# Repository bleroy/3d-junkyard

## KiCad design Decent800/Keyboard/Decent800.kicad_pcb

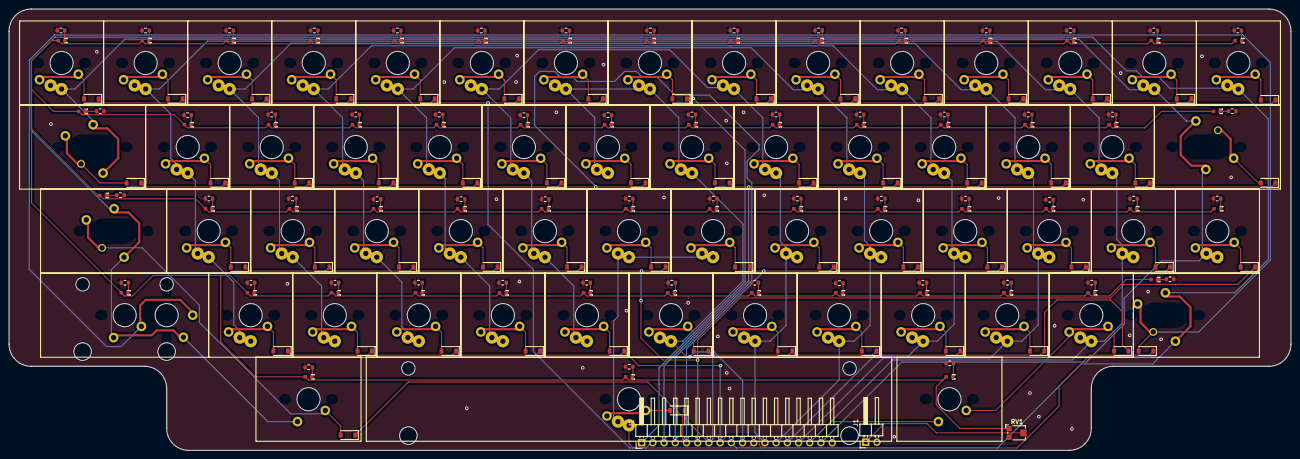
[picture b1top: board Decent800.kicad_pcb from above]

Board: 2 copper layers, 290.5 x 100.0 mm, 177 parts (0 on the bottom side), 135 nets.

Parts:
D1, D2, D3, D5, D6, D7, D8, D10, D12, D13, D14, D15, D16, D17, D18, D19, D20, D21, D22, D24, D25, D26, D27, D28, D29, D30, D31, D32, D33, D34, D35, D36, D37, D38, D39, D41, D42, D43, D44, D45, D46, D47, D48, D49, D50, D51, D52, D53, D54, D55, D56, D57, D58, D59, D60, D62: 1N4148W; D_SOD-123
J1: Conn_01x02_Pin; PinHeader_1x02_P2.54mm_Horizontal
J2: Conn_01x18; PinHeader_1x18_P2.54mm_Horizontal
R1, R2, R3, R4, R5, R7, R8, R9, R10, R11, R12, R14, R15, R16, R17, R18, R19, R20, R21, R22, R23, R24, R25, R26, R27, R28, R29, R30, R31, R32, R33, R34, R35, R36, R37, R38, R39, R40, R42, R43, R44, R45, R46, R47, R48, R49, R50, R51, R52, R53, R54, R55, R56, R57, R59, R60, R61, R62, R64: 100; R_0603_1608Metric
RV1: R_Potentiometer; Potentiometer_Bourns_TC33X_Vertical
SW0: 0; MX-1-00U-LED
SW1: 1; MX-1-00U-LED
SW2: 2; MX-1-00U-LED
SW3: 3; MX-1-00U-LED
SW4: 4; MX-1-00U-LED
SW5: 5; MX-1-00U-LED
SW6: 6; MX-1-00U-LED
SW7: 7; MX-1-00U-LED
SW8: 8; MX-1-00U-LED
SW9: 9; MX-1-00U-LED
SWA1: A; MX-1-00U-LED
SWAtari1: Atari; MX-1-00U-LED
SWAtari2: Atari; MX-1-25U-LED
SWB1: B; MX-1-00U-LED
SWBrk1: Break; MX-1-00U-LED
SWC1: C; MX-1-00U-LED
SWComma1: Comma; MX-1-00U-LED
SWCps1: Caps; MX-1-00U-LED
SWCtl1: Control; MX-1-50U-LED
SWCtl2: Control; MX-1-25U-LED
SWD1: D; MX-1-00U-LED
SWDash1: Dash; MX-1-00U-LED
SWDel1: Del; MX-1-00U-LED
SWE1: E; MX-1-00U-LED
SWEqual1: Equal; MX-1-00U-LED
SWEsc1: Esc; MX-1-00U-LED
SWF1: F; MX-1-00U-LED
SWG1: G; MX-1-00U-LED
SWGT1: GreaterThan; MX-1-00U-LED
SWH1: H; MX-1-00U-LED
SWI1: I; MX-1-00U-LED
SWJ1: J; MX-1-00U-LED
SWK1: K; MX-1-00U-LED
SWL1: L; MX-1-00U-LED
SWLT1: LessThan; MX-1-00U-LED
SWLeftSft1: Shift; MX-2-00U-LED
SWM1: M; MX-1-00U-LED
SWN1: N; MX-1-00U-LED
SWO1: O; MX-1-00U-LED
SWP1: P; MX-1-00U-LED
SWPeriod1: Period; MX-1-00U-LED
SWPlus1: Plus; MX-1-00U-LED
SWQ1: Q; MX-1-00U-LED
SWR1: R; MX-1-00U-LED
SWRet1: Return; MX-1-50U-LED-Right
SWRightSft1: Shift; MX-2-50U-LED
SWS1: S; MX-1-00U-LED
SWSemi1: Semicolon; MX-1-00U-LED
SWSlash1: Slash; MX-1-00U-LED
SWSpc1: Space; MX-6-25U-LED
SWStar1: Star; MX-1-00U-LED
SWT1: T; MX-1-00U-LED
SWTab1: Tab; MX-1-50U-LED
SWU1: U; MX-1-00U-LED
SWV1: V; MX-1-00U-LED
SWW1: W; MX-1-00U-LED
SWX1: X; MX-1-00U-LED
SWY1: Y; MX-1-00U-LED
SWZ1: Z; MX-1-00U-LED

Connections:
5V: J1.1, RV1.2
COL_1: J2.10, SW6.1, SW7.1, SWN1.1, SWU1.1, SWY1.1
COL_2: J2.11, SWH1.1, SWJ1.1, SWSpc1.1
COL_3: J2.12, SW5.1, SW8.1, SWB1.1, SWG1.1, SWI1.1, SWK1.1, SWM1.1, SWT1.1
COL_4: J2.13, SW4.1, SW9.1, SWComma1.1, SWF1.1, SWL1.1, SWO1.1, SWR1.1, SWV1.1
COL_5: J2.14, SW0.1, SW3.1, SWC1.1, SWD1.1, SWE1.1, SWP1.1, SWPeriod1.1, SWSemi1.1
COL_6: J2.15, SW2.1, SWDash1.1, SWLT1.1, SWPlus1.1, SWS1.1, SWSlash1.1, SWW1.1, SWX1.1
COL_7: J2.16, SW1.1, SWA1.1, SWAtari1.1, SWAtari2.1, SWEqual1.1, SWGT1.1, SWQ1.1, SWStar1.1, SWZ1.1
COL_8: J2.17, SWCps1.1, SWDel1.1, SWEsc1.1, SWRet1.1, SWTab1.1
COL_9: J2.9, SWBrk1.1, SWCtl1.1, SWCtl2.1, SWLeftSft1.1, SWRightSft1.1
LED_GND: J1.2, R1.2, R2.2, R3.2, R4.2, R5.2, R7.2, R8.2, R9.2, R10.2, R11.2, R12.2, R14.2, R15.2, R16.2, R17.2, R18.2, R19.2, R20.2, R21.2, R22.2, R23.2, R24.2, R25.2, R26.2, R27.2, R28.2, R29.2, R30.2, R31.2, R32.2, R33.2, R34.2, R35.2, R36.2, R37.2, R38.2, R39.2, R40.2, R42.2, R43.2, R44.2, R45.2, R46.2, R47.2, R48.2, R49.2, R50.2, R51.2, R52.2, R53.2, R54.2, R55.2, R56.2, R57.2, R59.2, R60.2, R61.2, R62.2, R64.2
unnamed: D1.2 (A), SWBrk1.2
unnamed: D2.2 (A), SWCtl1.2, SWCtl2.2
unnamed: D3.2 (A), SWLeftSft1.2, SWRightSft1.2
unnamed: D5.2 (A), SW7.2
unnamed: D6.2 (A), SW6.2
unnamed: D7.2 (A), SWU1.2
unnamed: D8.2 (A), SWY1.2
unnamed: D10.2 (A), SWN1.2
unnamed: D12.2 (A), SWJ1.2
unnamed: D13.2 (A), SWH1.2
unnamed: D14.2 (A), SWSpc1.2
unnamed: D15.2 (A), SW8.2
unnamed: D16.2 (A), SW5.2
unnamed: D17.2 (A), SWI1.2
unnamed: D18.2 (A), SWT1.2
unnamed: D19.2 (A), SWK1.2
unnamed: D20.2 (A), SWG1.2
unnamed: D21.2 (A), SWM1.2
unnamed: D22.2 (A), SWB1.2
unnamed: D24.2 (A), SW9.2
unnamed: D25.2 (A), SW4.2
unnamed: D26.2 (A), SWO1.2
unnamed: D27.2 (A), SWR1.2
unnamed: D28.2 (A), SWL1.2
unnamed: D29.2 (A), SWF1.2
unnamed: D30.2 (A), SWComma1.2
unnamed: D31.2 (A), SWV1.2
unnamed: D32.2 (A), SW0.2
unnamed: D33.2 (A), SW3.2
unnamed: D34.2 (A), SWP1.2
unnamed: D35.2 (A), SWE1.2
unnamed: D36.2 (A), SWSemi1.2
unnamed: D37.2 (A), SWD1.2
unnamed: D38.2 (A), SWPeriod1.2
unnamed: D39.2 (A), SWC1.2
unnamed: D41.2 (A), SWLT1.2
unnamed: D42.2 (A), SW2.2
unnamed: D43.2 (A), SWDash1.2
unnamed: D44.2 (A), SWW1.2
unnamed: D45.2 (A), SWPlus1.2
unnamed: D46.2 (A), SWS1.2
unnamed: D47.2 (A), SWSlash1.2
unnamed: D48.2 (A), SWX1.2
unnamed: D49.2 (A), SWGT1.2
unnamed: D50.2 (A), SW1.2
unnamed: D51.2 (A), SWEqual1.2
unnamed: D52.2 (A), SWQ1.2
unnamed: D53.2 (A), SWStar1.2
unnamed: D54.2 (A), SWA1.2
unnamed: D55.2 (A), SWAtari1.2, SWAtari2.2
unnamed: D56.2 (A), SWZ1.2
unnamed: D57.2 (A), SWDel1.2
unnamed: D58.2 (A), SWEsc1.2
unnamed: D59.2 (A), SWRet1.2
unnamed: D60.2 (A), SWTab1.2
unnamed: D62.2 (A), SWCps1.2
unnamed: R1.1, SWBrk1.3
unnamed: R2.1, SWAtari2.3
unnamed: R3.1, SWCtl1.3
unnamed: R4.1, SWLeftSft1.3
unnamed: R5.1, SWRightSft1.3
unnamed: R7.1, SW7.3
unnamed: R8.1, SW6.3
unnamed: R9.1, SWU1.3
unnamed: R10.1, SWY1.3
unnamed: R11.1, SWCtl2.3
unnamed: R12.1, SWN1.3
unnamed: R14.1, SWJ1.3
unnamed: R15.1, SWH1.3
unnamed: R16.1, SWSpc1.3
unnamed: R17.1, SW8.3
unnamed: R18.1, SW5.3
unnamed: R19.1, SWI1.3
unnamed: R20.1, SWT1.3
unnamed: R21.1, SWK1.3
unnamed: R22.1, SWG1.3
unnamed: R23.1, SWM1.3
unnamed: R24.1, SWB1.3
unnamed: R25.1, SW9.3
unnamed: R26.1, SW4.3
unnamed: R27.1, SWO1.3
unnamed: R28.1, SWR1.3
unnamed: R29.1, SWL1.3
unnamed: R30.1, SWF1.3
unnamed: R31.1, SWComma1.3
unnamed: R32.1, SWV1.3
unnamed: R33.1, SW0.3
unnamed: R34.1, SW3.3
unnamed: R35.1, SWP1.3
unnamed: R36.1, SWE1.3
unnamed: R37.1, SWSemi1.3
unnamed: R38.1, SWD1.3
unnamed: R39.1, SWPeriod1.3
unnamed: R40.1, SWC1.3
unnamed: R42.1, SWLT1.3
unnamed: R43.1, SW2.3
unnamed: R44.1, SWDash1.3
unnamed: R45.1, SWW1.3
unnamed: R46.1, SWPlus1.3
unnamed: R47.1, SWS1.3
unnamed: R48.1, SWSlash1.3
unnamed: R49.1, SWX1.3
unnamed: R50.1, SWGT1.3
unnamed: R51.1, SW1.3
unnamed: R52.1, SWEqual1.3
unnamed: R53.1, SWQ1.3
unnamed: R54.1, SWStar1.3
unnamed: R55.1, SWA1.3
unnamed: R56.1, SWAtari1.3
unnamed: R57.1, SWZ1.3
unnamed: R59.1, SWDel1.3
unnamed: R60.1, SWEsc1.3
unnamed: R61.1, SWRet1.3
unnamed: R62.1, SWTab1.3
unnamed: R64.1, SWCps1.3
ROW_1: D1.1 (K), D5.1 (K), D15.1 (K), D24.1 (K), D32.1 (K), D41.1 (K), D49.1 (K), D57.1 (K), J2.1
ROW_2: D6.1 (K), D16.1 (K), D25.1 (K), D33.1 (K), D42.1 (K), D50.1 (K), D58.1 (K), J2.2
ROW_3: D7.1 (K), D17.1 (K), D26.1 (K), D34.1 (K), D43.1 (K), D51.1 (K), D59.1 (K), J2.3
ROW_4: D8.1 (K), D18.1 (K), D27.1 (K), D35.1 (K), D44.1 (K), D52.1 (K), D60.1 (K), J2.4
ROW_5: D2.1 (K), D12.1 (K), D19.1 (K), D28.1 (K), D36.1 (K), D45.1 (K), D53.1 (K), J2.5
ROW_6: D13.1 (K), D20.1 (K), D29.1 (K), D37.1 (K), D46.1 (K), D54.1 (K), D62.1 (K), J2.6
ROW_7: D10.1 (K), D14.1 (K), D21.1 (K), D30.1 (K), D38.1 (K), D47.1 (K), D55.1 (K), J2.7
ROW_8: D3.1 (K), D22.1 (K), D31.1 (K), D39.1 (K), D48.1 (K), D56.1 (K), J2.8
VCC_LED: RV1.1, SW0.4, SW1.4, SW2.4, SW3.4, SW4.4, SW5.4, SW6.4, SW7.4, SW8.4, SW9.4, SWA1.4, SWAtari1.4, SWAtari2.4, SWB1.4, SWBrk1.4, SWC1.4, SWComma1.4, SWCps1.4, SWCtl1.4, SWCtl2.4, SWD1.4, SWDash1.4, SWDel1.4, SWE1.4, SWEqual1.4, SWEsc1.4, SWF1.4, SWG1.4, SWGT1.4, SWH1.4, SWI1.4, SWJ1.4, SWK1.4, SWL1.4, SWLT1.4, SWLeftSft1.4, SWM1.4, SWN1.4, SWO1.4, SWP1.4, SWPeriod1.4, SWPlus1.4, SWQ1.4, SWR1.4, SWRet1.4, SWRightSft1.4, SWS1.4, SWSemi1.4, SWSlash1.4, SWSpc1.4, SWStar1.4, SWT1.4, SWTab1.4, SWU1.4, SWV1.4, SWW1.4, SWX1.4, SWY1.4, SWZ1.4

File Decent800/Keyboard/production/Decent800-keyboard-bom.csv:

Designator,Footprint,Quantity,Value,LCSC Part #
"D1, D10, D12, D13, D14, D15, D16, D17, D18, D19, D2, D20, D21, D22, D24, D25, D26, D27, D28, D29, D3, D30, D31, D32, D33, D34, D35, D36, D37, D38, D39, D41, D42, D43, D44, D45, D46, D47, D48, D49, D5, D50, D51, D52, D53, D54, D55, D56, D57, D58, D59, D6, D60, D62, D7, D8",D_SOD-123,56,1N4148W,C81598
"R10, R11, R12, R14, R15, R16, R17, R18, R19, R2, R20, R21, R22, R23, R24, R25, R26, R27, R28, R29, R3, R30, R31, R32, R33, R34, R35, R36, R37, R38, R39, R4, R40, R42, R43, R44, R45, R46, R47, R48, R49, R5, R50, R51, R52, R53, R54, R55, R56, R57, R6, R60, R61, R62, R64, R7, R8, R9",0603,58,100,C22775
RV1,Potentiometer_Bourns_TC33X_Vertical,1,R_Potentiometer,C720647
SW0,MX-1-00U-LED,1,0,C193191
SW1,MX-1-00U-LED,1,1,C193191
SW2,MX-1-00U-LED,1,2,C193191
SW3,MX-1-00U-LED,1,3,C193191
SW4,MX-1-00U-LED,1,4,C193191
SW5,MX-1-00U-LED,1,5,C193191
SW6,MX-1-00U-LED,1,6,C193191
SW7,MX-1-00U-LED,1,7,C193191
SW8,MX-1-00U-LED,1,8,C193191
SW9,MX-1-00U-LED,1,9,C193191
SWA1,MX-1-00U-LED,1,A,C193191
SWAtari1,Choc-1-00U-LED,1,Atari,C193191
SWAtari2,MX-1-25U-LED,1,Atari,C193191
SWB1,MX-1-00U-LED,1,B,C193191
SWBrk2,MX-1-25U-LED,1,Break,C193191
SWC1,MX-1-00U-LED,1,C,C193191
SWComma1,MX-1-00U-LED,1,Comma,C193191
SWCps1,MX-1-00U-LED,1,Caps,C193191
SWCtl1,MX-1-50U-LED,1,Control,C193191
SWD1,MX-1-00U-LED,1,D,C193191
SWDash1,MX-1-00U-LED,1,Dash,C193191
SWDel2,MX-2-00U-LED-Del,1,Del,C193191
SWE1,MX-1-00U-LED,1,E,C193191
SWEqual1,MX-1-00U-LED,1,Equal,C193191
SWEsc1,MX-1-00U-LED,1,Esc,C193191
SWF1,MX-1-00U-LED,1,F,C193191
SWG1,MX-1-00U-LED,1,G,C193191
SWGT1,MX-1-00U-LED,1,GreaterThan,C193191
SWH1,MX-1-00U-LED,1,H,C193191
SWI1,MX-1-00U-LED,1,I,C193191
SWJ1,MX-1-00U-LED,1,J,C193191
SWK1,MX-1-00U-LED,1,K,C193191
SWL1,MX-1-00U-LED,1,L,C193191
SWLT1,MX-1-00U-LED,1,LessThan,C193191
SWLeftSft1,MX-2-00U-LED,1,Shift,C193191
SWM1,MX-1-00U-LED,1,M,C193191
SWN1,MX-1-00U-LED,1,N,C193191
SWO1,MX-1-00U-LED,1,O,C193191
SWP1,MX-1-00U-LED,1,P,C193191
SWPeriod1,MX-1-00U-LED,1,Period,C193191
SWPlus1,MX-1-00U-LED,1,Plus,C193191
SWQ1,MX-1-00U-LED,1,Q,C193191
SWR1,MX-1-00U-LED,1,R,C193191
SWRet1,MX-1-50U-LED-Right,1,Return,C193191
SWRightSft1,MX-2-25U-LED,1,Shift,C193191
SWS1,MX-1-00U-LED,1,S,C193191
SWSemi1,MX-1-00U-LED,1,Semicolon,C193191
SWSlash1,MX-1-00--1-25U-LED,1,Slash,C193191
SWSpc1,MX-6-25U-LED,1,Space,C193191
SWStar1,MX-1-00U-LED,1,Star,C193191
SWT1,MX-1-00U-LED,1,T,C193191
SWTab1,MX-1-50U-LED,1,Tab,C193191
SWU1,MX-1-00U-LED,1,U,C193191
SWV1,MX-1-00U-LED,1,V,C193191
SWW1,MX-1-00U-LED,1,W,C193191
SWX1,MX-1-00U-LED,1,X,C193191
SWY1,MX-1-00U-LED,1,Y,C193191
SWZ1,MX-1-00U-LED,1,Z,C193191

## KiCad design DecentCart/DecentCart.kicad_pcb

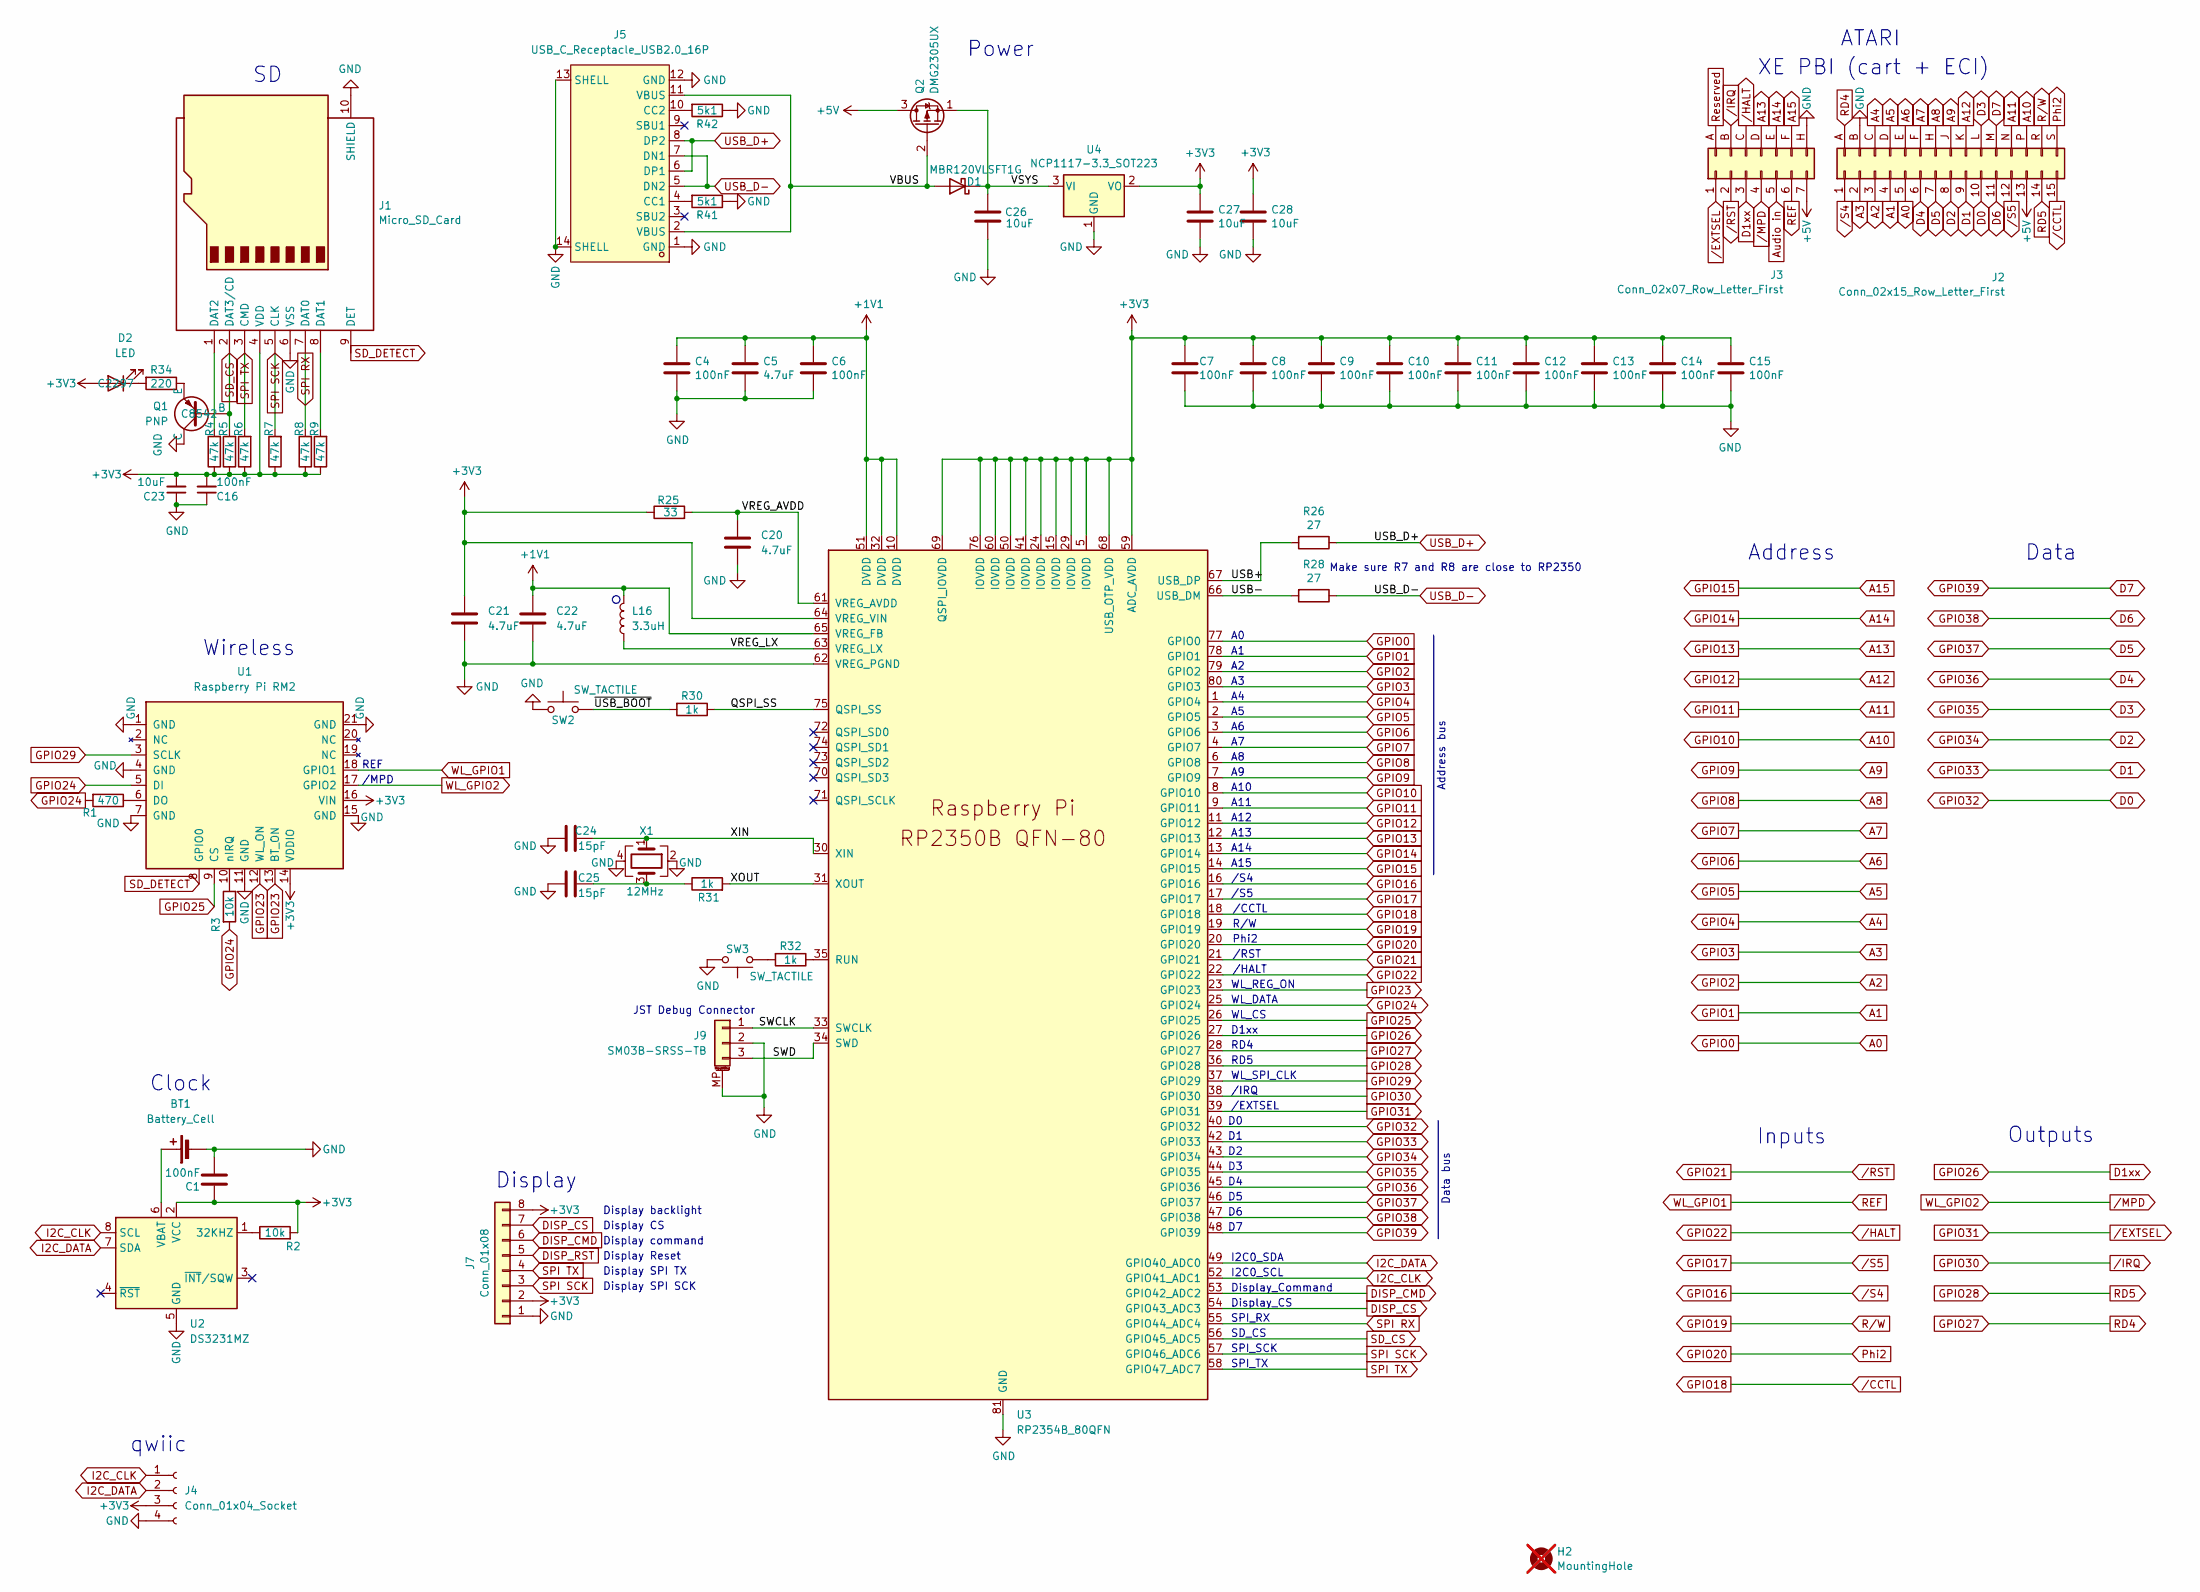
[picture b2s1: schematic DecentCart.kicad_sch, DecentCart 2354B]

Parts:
BT1: Battery_Cell; BAT-SMD_BS-CR2032-8; JLCPCB Part # C70377
C1, C4, C6, C7, C8, C9, C10, C11, C12, C13, C14, C15, C16: 100nF; C_0402_1005Metric; JLCPCB Part # C1525
C5, C20: 4.7uF; C_0402_1005Metric; JLCPCB Part # C23733
C21, C22: 4.7uF; C_0603_1608Metric; JLCPCB Part # C19666
C23, C26, C27, C28: 10uF; C_0402_1005Metric; JLCPCB Part # C15525
C24, C25: 15pF; C_0402_1005Metric; JLCPCB Part # C1548
D1: MBR120VLSFT1G; Nexperia_CFP3_SOD-123W; JLCPCB Part # C8598
D2: LED; D_0805_2012Metric; JLCPCB Part # C2297
H2: MountingHole; MountingHole_2.2mm_M2; not fitted
J1: Micro_SD_Card; TF-SMD_TF-PUSH; JLCPCB Part # C393941
J2: Conn_02x15_Row_Letter_First; Atari Cartridge Edge Connector
J3: Conn_02x07_Row_Letter_First; IDC-SMD_14P-P1.27_HXJN1.27-14P_ATARI_ECI; JLCPCB Part # C42455944
J4: Conn_01x04_Socket; CONN-SMD_4P-P1.00_SM04B-SRSS-TB-LF-SN; JLCPCB Part # C160404
J5: USB_C_Receptacle_USB2.0_16P; USB-C-SMD_TYPE-C-6PIN-2MD-073; JLCPCB Part # C2765186
J7: Conn_01x08; PinHeader_1x08_P2.54mm_Vertical
J9: SM03B-SRSS-TB; JST_SH_SM03B-SRSS-TB_1x03-1MP_P1.00mm_Horizontal; JLCPCB Part # C160389
L16: 3.3uH; IND-SMD_L2.0-W1.6_AOTA-B201610S3R3-101-T; JLCPCB Part # C42411119
Q1: PNP; SOT-23; JLCPCB Part # C8542
Q2: DMG2305UX; SOT-23; JLCPCB Part # C150470
R1: 470; R_0402_1005Metric; JLCPCB Part # C25117
R2, R3: 10k; R_0402_1005Metric; JLCPCB Part # C25744
R4, R5, R6, R7, R8, R9: 47k; R_0402_1005Metric; JLCPCB Part # C25792
R25: 33; R_0402_1005Metric; JLCPCB Part # C25105
R26, R28: 27; R_0805_2012Metric; JLCPCB Part # C17561
R30, R31, R32: 1k; R_0402_1005Metric; JLCPCB Part # C11702
R34: 220; R_0402_1005Metric; JLCPCB Part # C25091
R41, R42: 5k1; R_0402_1005Metric; JLCPCB Part # C25905
SW2, SW3: SW_TACTILE; Tactile_Switch_Basic_XKB_TS-1187A; JLCPCB Part # C318884
U1: Raspberry Pi RM2; rpi_rmc20452t; JLCPCB Part # C49451547
U2: DS3231MZ; SOIC-8_3.9x4.9mm_P1.27mm; JLCPCB Part # C107410
U3: RP2354B_80QFN; QFN-80_L10.0-W10.0-P0.40-TL-EP3.4; JLCPCB Part # C39843328
U4: NCP1117-3.3_SOT223; SOT-223-3_TabPin2; JLCPCB Part # C6186
X1: 12MHz; Crystal_SMD_Abracon_ABM8AIG-4Pin_3.2x2.5mm; JLCPCB Part # C20625731

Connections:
+1V1: C4.1, C5.1, C6.1, C22.1, L16.2, U3.10 (DVDD), U3.32 (DVDD), U3.51 (DVDD), U3.65 (VREG_FB)
+3V3: C1.1, C7.1, C8.1, C9.1, C10.1, C11.1, C12.1, C13.1, C14.1, C15.1, C16.2, C21.1, C23.2, C27.1, C28.1, D2.2 (A), J1.4 (VDD), J4.3, J7.2, J7.8, R2.2, R4.1, R5.1, R6.1, R7.1, R8.1, R9.1, R25.1, U1.14 (VDDIO), U1.16 (VIN), U2.2 (VCC), U3.5 (IOVDD), U3.15 (IOVDD), U3.24 (IOVDD), U3.29 (IOVDD), U3.41 (IOVDD), U3.50 (IOVDD), U3.59 (ADC_AVDD), U3.60 (IOVDD), U3.64 (VREG_VIN), U3.68 (USB_OTP_VDD), U3.69 (QSPI_IOVDD), U3.76 (IOVDD), U4.2 (VO)
+5V: J2.13, J3.7, Q2.3 (D)
/QSPI_SS: R30.1, U3.75 (QSPI_SS)
/SWCLK: J9.1, U3.33 (SWCLK)
/SWD: J9.3, U3.34 (SWD)
/USB+: R26.2, U3.67 (USB_DP)
/USB-: R28.2, U3.66 (USB_DM)
/VBUS: D1.2 (A), J5.2 (VBUS), J5.11 (VBUS), Q2.2 (G)
/VREG_AVDD: C20.1, R25.2, U3.61 (VREG_AVDD)
/VREG_LX: L16.1, U3.63 (VREG_LX)
/XIN: C24.1, U3.30 (XIN), X1.1
/XOUT: R31.2, U3.31 (XOUT)
/~USB_BOOT: R30.2, SW2.2
A0: J2.5, U3.77 (GPIO0)
A1: J2.4, U3.78 (GPIO1)
A2: J2.3, U3.79 (GPIO2)
A3: J2.2, U3.80 (GPIO3)
A4: J2.C, U3.1 (GPIO4)
A5: J2.D, U3.2 (GPIO5)
A6: J2.E, U3.3 (GPIO6)
A7: J2.F, U3.4 (GPIO7)
A8: J2.H, U3.6 (GPIO8)
A9: J2.J, U3.7 (GPIO9)
A10: J2.P, U3.8 (GPIO10)
A11: J2.N, U3.9 (GPIO11)
A12: J2.K, U3.11 (GPIO12)
A13: J3.D, U3.12 (GPIO13)
A14: J3.E, U3.13 (GPIO14)
A15: J3.F, U3.14 (GPIO15)
Audio in: J3.5
D0: J2.10, U3.40 (GPIO32)
D1: J2.9, U3.42 (GPIO33)
D1xx: J3.3, U3.27 (GPIO26)
D2: J2.8, U3.43 (GPIO34)
D3: J2.L, U3.44 (GPIO35)
D4: J2.6, U3.45 (GPIO36)
D5: J2.7, U3.46 (GPIO37)
D6: J2.11, U3.47 (GPIO38)
D7: J2.M, U3.48 (GPIO39)
DISP_CMD: J7.6, U3.53 (GPIO42_ADC2)
DISP_CS: J7.7, U3.54 (GPIO43_ADC3)
DISP_RST: J7.5
GND: BT1.2 (-), C1.2, C4.2, C5.2, C6.2, C7.2, C8.2, C9.2, C10.2, C11.2, C12.2, C13.2, C14.2, C15.2, C16.1, C20.2, C21.2, C22.2, C23.1, C24.2, C25.1, C26.2, C27.2, C28.2, J1.6 (VSS), J1.10 (SHIELD), J2.B, J3.H, J4.4, J5.1 (GND), J5.12 (GND), J5.13 (SHELL), J5.14 (SHELL), J7.1, J9.2, J9.MP (MountPin), Q1.1 (C), R41.1, R42.1, SW2.1, SW3.2, U1.1 (GND), U1.4 (GND), U1.7 (GND), U1.11 (GND), U1.15 (GND), U1.21 (GND), U2.5 (GND), U3.62 (VREG_PGND), U3.81 (GND), U4.1 (GND), X1.2, X1.4
GPIO16: J2.1, U3.16 (GPIO16)
GPIO17: J2.12, U3.17 (GPIO17)
GPIO18: J2.15, U3.18 (GPIO18)
GPIO19: J2.R, U3.19 (GPIO19)
GPIO20: J2.S, U3.20 (GPIO20)
GPIO21: J3.2, U3.21 (GPIO21)
GPIO22: J3.C, U3.22 (GPIO22)
GPIO23: U1.12 (WL_ON), U1.13 (BT_ON), U3.23 (GPIO23)
GPIO24: R1.2, R3.2, U1.5 (DI), U3.25 (GPIO24)
GPIO25: U1.9 (CS), U3.26 (GPIO25)
GPIO27: J2.A, U3.28 (GPIO27)
GPIO28: J2.14, U3.36 (GPIO28)
GPIO29: U1.3 (SCLK), U3.37 (GPIO29)
GPIO30: J3.B, U3.38 (GPIO30)
GPIO31: J3.1, U3.39 (GPIO31)
I2C_CLK: J4.1, U2.8 (SCL), U3.52 (GPIO41_ADC1)
I2C_DATA: J4.2, U2.7 (SDA), U3.49 (GPIO40_ADC0)
unnamed: BT1.1 (+), U2.6 (VBAT)
unnamed: C25.2, R31.1, X1.3
unnamed: C26.1, D1.1 (K), Q2.1 (S), U4.3 (VI)
unnamed: D2.1 (K), R34.2
unnamed: J1.8 (DAT1), R9.2
unnamed: J1.1 (DAT2), R4.2
unnamed: J5.4 (CC1), R41.2
unnamed: J5.10 (CC2), R42.2
unnamed: Q1.3 (E), R34.1
unnamed: R32.2, SW3.1
unnamed: R1.1, U1.6 (DO)
unnamed: R3.1, U1.10 (nIRQ)
unnamed: R2.1, U2.1 (32KHZ)
unnamed: R32.1, U3.35 (RUN)
REF: J3.6, U1.18 (GPIO1)
Reserved: J3.A
SD_CS: J1.2 (DAT3/CD), Q1.2 (B), R5.2, U3.56 (GPIO45_ADC5)
SD_DETECT: J1.9 (DET), U1.8 (GPIO0)
SPI RX: J1.7 (DAT0), R8.2, U3.55 (GPIO44_ADC4)
SPI SCK: J1.5 (CLK), J7.3, R7.2, U3.57 (GPIO46_ADC6)
SPI TX: J1.3 (CMD), J7.4, R6.2, U3.58 (GPIO47_ADC7)
USB_D+: J5.6 (DP1), J5.8 (DP2), R26.1
USB_D-: J5.5 (DN2), J5.7 (DN1), R28.1
WL_GPIO2: J3.4, U1.17 (GPIO2)

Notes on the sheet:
Clock
A10
SPI_SCK
XE PBI (cart + ECI)
SPI_TX
Display Reset
A14
ATARI
Display command
WL_CS
Display
Address bus
Data bus
Display_CS
D1xx
Power
SD_CS
WL_REG_ON
WL_SPI_CLK
Inputs
Wireless
A12
Make sure R7 and R8 are close to RP2350
/CCTL
Data
Display_Command
Display SPI SCK
RD4
JST Debug Connector
Outputs
/IRQ
Phi2
I2C0_SDA
Display SPI TX
I2C0_SCL
A15
WL_DATA
R/W
SPI_RX
A13

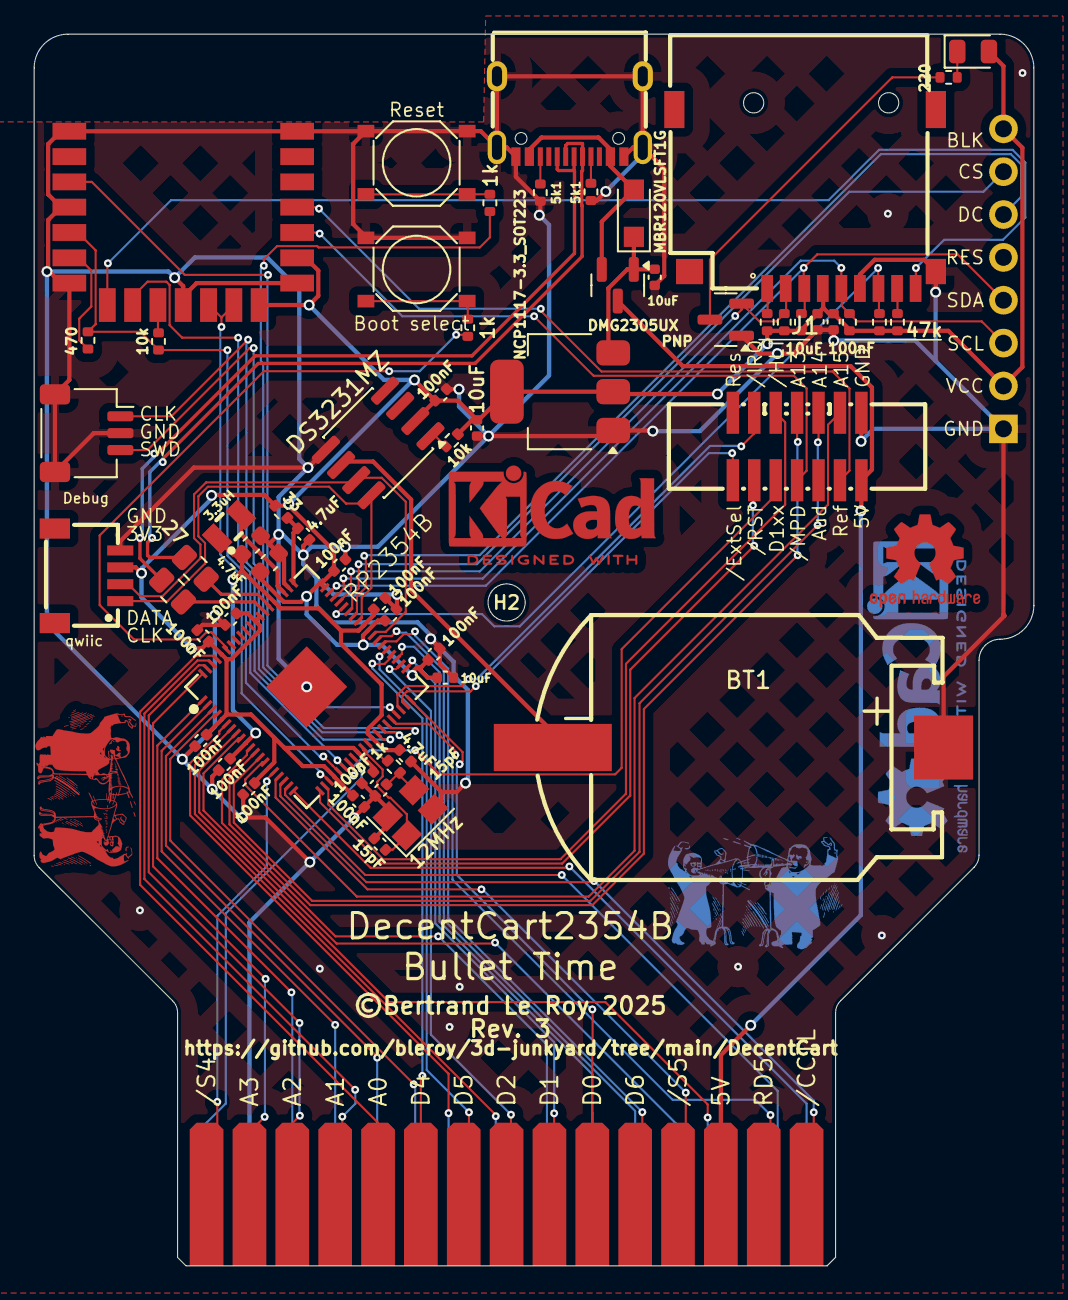
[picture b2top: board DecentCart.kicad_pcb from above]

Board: 2 copper layers, 59.3 x 73.0 mm, 62 parts (1 on the bottom side), 82 nets.

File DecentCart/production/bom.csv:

Designator,Footprint,Quantity,Value,LCSC Part #
BT1,BAT-SMD_BS-CR2032-8,1,Battery_Cell,C70377
"C1, C10, C11, C12, C13, C14, C15, C16, C4, C6, C7, C8, C9",0402,13,100nF,C1525
"C20, C5",0402,2,4.7uF,C23733
"C21, C22",0603,2,4.7uF,C19666
"C23, C26, C27, C28",0402,4,10uF,C15525
"C24, C25",0402,2,15pF,C1548
D1,Nexperia_CFP3_SOD-123W,1,MBR120VLSFT1G,C8598
D2,0805,1,LED,C2297
J1,TF-SMD_TF-PUSH,1,Micro_SD_Card,C393941
J2,Atari Cartridge Edge Connector,1,Conn_02x15_Row_Letter_First,
J3,IDC-SMD_14P-P1.27_HXJN1.27-14P_ATARI_ECI,1,Conn_02x07_Row_Letter_First,C42455944
J4,CONN-SMD_4P-P1.00_SM04B-SRSS-TB-LF-SN,1,Conn_01x04_Socket,C160404
J5,USB-C-SMD_TYPE-C-6PIN-2MD-073,1,USB_C_Receptacle_USB2.0_16P,C2765186
J9,JST_SH_SM03B-SRSS-TB_1x03-1MP_P1.00mm_Horizontal,1,SM03B-SRSS-TB,C160389
L16,IND-SMD_L2.0-W1.6_AOTA-B201610S3R3-101-T,1,3.3uH,C42411119
Q1,SOT-23,1,PNP,C8542
Q2,SOT-23,1,DMG2305UX,C150470
R1,0402,1,470,C25117
"R2, R3",0402,2,10k,C25744
R25,0402,1,33,C25105
"R26, R28",0805,2,27,C17561
"R30, R31, R32",0402,3,1k,C11702
R34,0402,1,220,C25091
"R4, R5, R6, R7, R8, R9",0402,6,47k,C25792
"R41, R42",0402,2,5k1,C25905
"SW2, SW3",Tactile_Switch_Basic_XKB_TS-1187A,2,SW_TACTILE,C318884
U1,rpi_rmc20452t,1,Raspberry Pi RM2,C49451547
U2,SOIC-8_3.9x4.9mm_P1.27mm,1,DS3231MZ,C107410
U3,QFN-80_L10.0-W10.0-P0.40-TL-EP3.4,1,RP2354B_80QFN,C39843328
U4,SOT-223-3_TabPin2,1,NCP1117-3.3_SOT223,C6186
X1,Crystal_SMD_Abracon_ABM8AIG-4Pin_3.2x2.5mm,1,12MHz,C20625731

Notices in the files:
DecentCart/DecentCart.kicad_pcb:
©Bertrand Le Roy 2025
DecentCart/DecentCart2040/DecentCart2040.kicad_pcb:
©Bertrand Le Roy 2024
